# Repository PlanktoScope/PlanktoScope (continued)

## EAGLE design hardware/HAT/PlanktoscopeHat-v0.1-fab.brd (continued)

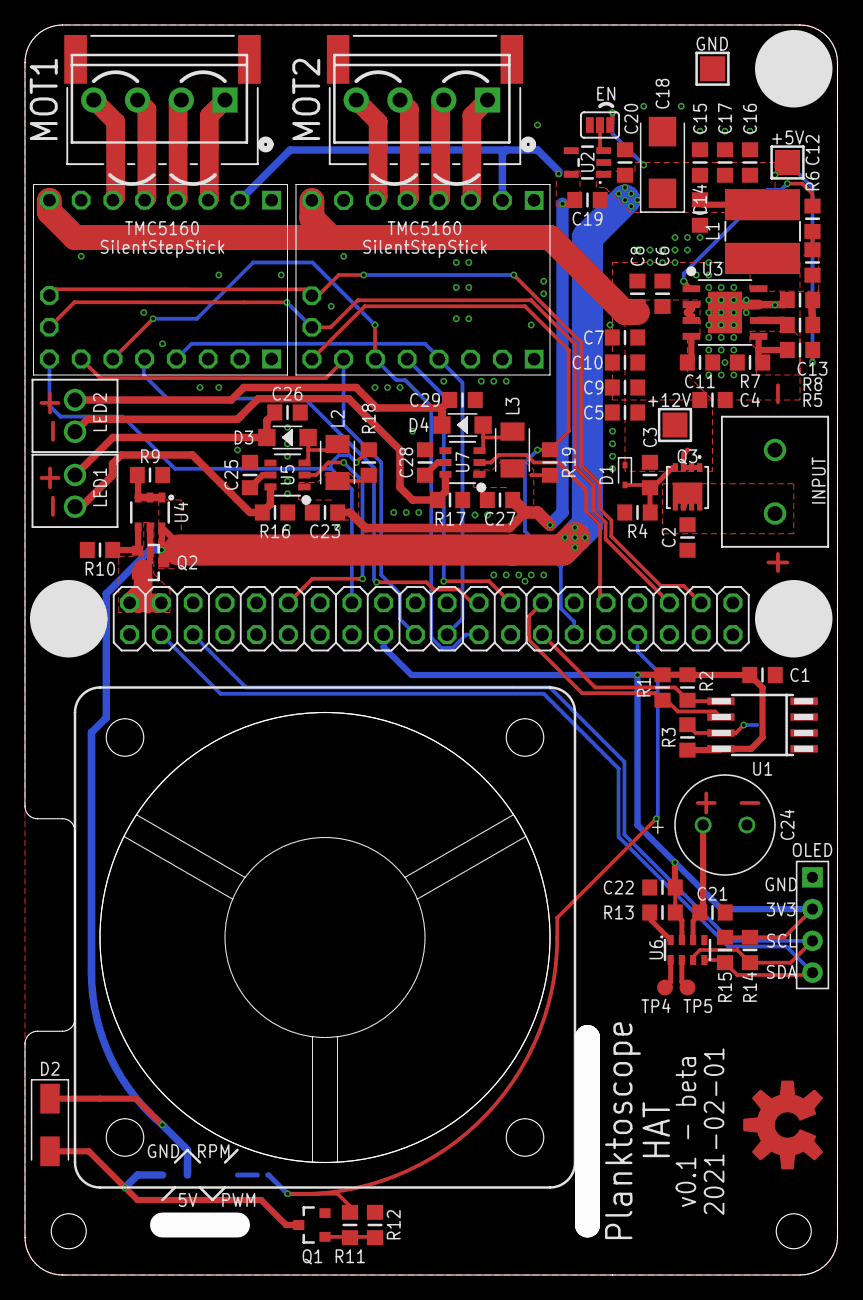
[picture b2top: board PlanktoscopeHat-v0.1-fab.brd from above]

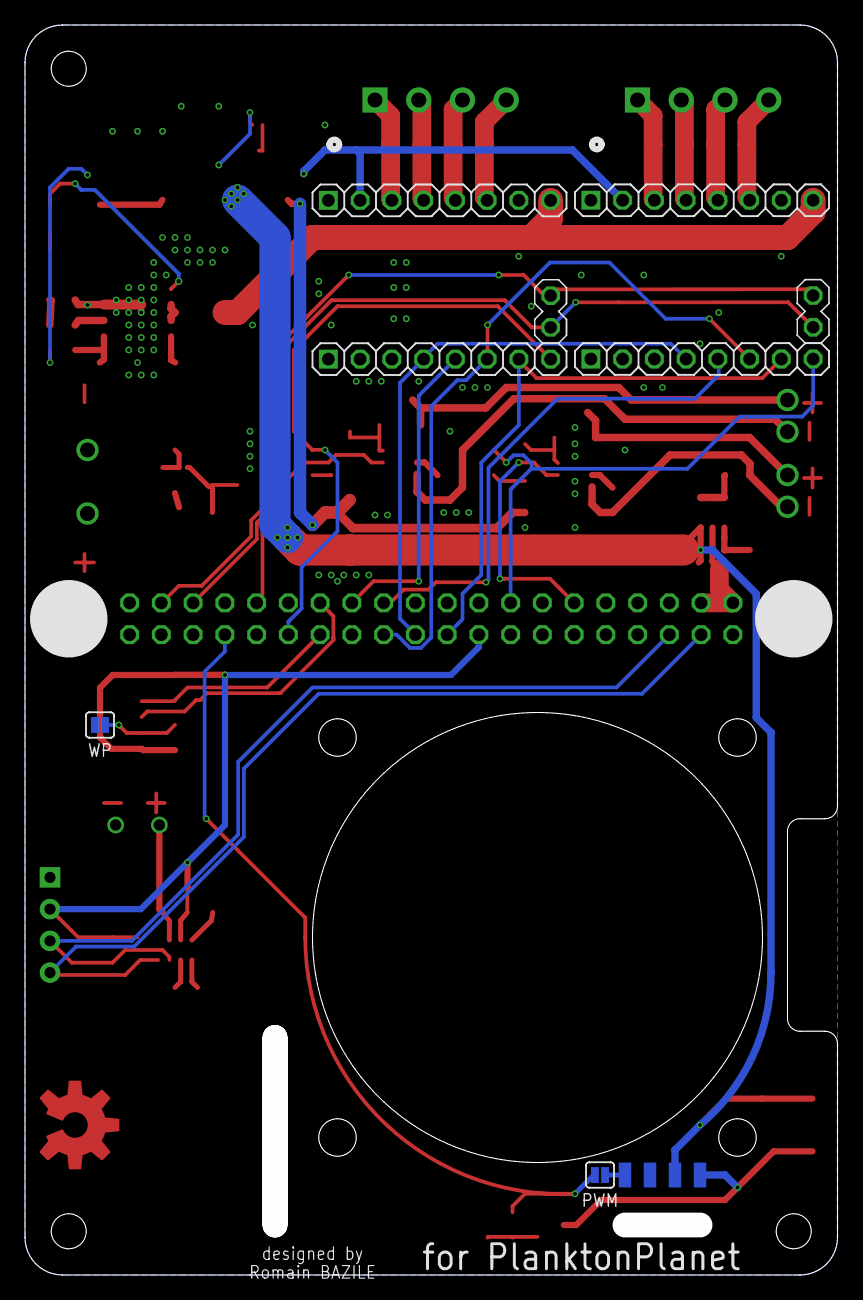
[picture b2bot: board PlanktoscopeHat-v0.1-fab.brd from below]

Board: 2 copper layers, 65.0 x 100.0 mm, 90 parts (8 on the bottom side), 58 nets.

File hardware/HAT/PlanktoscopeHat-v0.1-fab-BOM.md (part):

Qty|Value             |Device                      |Package             |Parts                          |Description                                       |MPN                  |Order Link |Alternative MPN | Alternative Order Link
:-:|----------------|----------------------------|--------------------|-------------------------------|--------------------------------------------------|---------------------|-----------|----------------|-----------------------
1  |1.2nF             |Capacitor Ceramic           |0805                |C13                            |Ceramic Capacitors                                |C0805C122K5RACTU     |https://www.mouser.fr/ProductDetail/KEMET/C0805C122K5RACTU/?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|                |
7  |100nF 100V        |Capacitor Ceramic           |0805                |C1, C2, C3, C11, C12 , C21, C22|Ceramic Capacitors                                |CL21B104KCFSFNE      |https://www.mouser.fr/ProductDetail/Samsung-Electro-Mechanic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 | |
2  |220nF             |Capacitor Ceramic           |0805                |C25, C28                       |Ceramic Capacitors                                |CL21B224KBFNNNG      |https://www.mouser.fr/ProductDetail/Samsung-Electro-Mechanic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 | | 
5  |10uF              |Capacitor Ceramic           |0805                |C14, C15, C16, C17, C19        |Ceramic Capacitors                                |CL21A106KOQNNNG      |https://www.mouser.fr/ProductDetail/Samsung-Electro-Mechanic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 | |
7  |10uF 35V          |Capacitor Ceramic           |0805                |C4, C5, C6, C7, C8, C9, C10    |Ceramic Capacitors                                |GRM21BR61H106KE43L   |https://www.mouser.fr/ProductDetail/Murata-Electronics/GRM21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 | |
1  |100µF 10VDC       |Capacitor Polarised Tantalum|2412 (6032 metric)  |C18                            |Capacitor Polarised                               |TPSC107K010T0200     |https://www.mouser.fr/ProductDetail/AVX/TPSC107K010T0200/?qs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 | |
3  |1µF               |Capacitor Ceramic           |0805                |C26, C29, C20                  |Ceramic Capacitors                                |CL21B105KAFNFNE      |https://www.mouser.fr/ProductDetail/Samsung-Electro-Mechanic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 | | 
2  |4.7µF             |Capacitor Ceramic           |0805                |C23, C27                       |Ceramic Capacitors                                |CL21A475KAQNNNG      |https://www.mouser.fr/ProductDetail/Samsung-Electro-Mechanic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 | | 
1  |1F-10F 3V         |Supercap                    |8X3.5X0.9           |C24                            |WCAP-PTHT Aluminum Polymer Capacitors             |DSF106Q3R0           |https://www.mouser.fr/ProductDetail/Cornell-Dubilier-CDE/DSF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 |SCCR16E205PRB |https://www.mouser.fr/ProductDetail/AVX/SCCR16E205PRB/?qs=qS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
2  |2R / 10R          |Resistor                    |0805                |R16, R17                       |Resistors                                         |CRCW08052R00FKEA     |https://www.mouser.fr/ProductDetail/Vishay-Dale/CRCW08052R00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 | | 
1  |10R               |Resistor                    |0805                |R6                             |Resistors                                         |CRCW080510R0FKEAC    |https://www.mouser.fr/ProductDetail/Vishay-Dale/CRCW080510R0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 | |
1  |499R              |Resistor                    |0805                |R11                            |Resistors                                         |CR0805-FX-4990ELF    |https://www.mouser.fr/ProductDetail/Bourns/CR0805-FX-4990ELF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 | | 
1  |1k                |Resistor                    |0805                |R3                             |Resistors                                         |CRCW08051K00FKEAC    |https://www.mouser.fr/ProductDetail/Vishay-Dale/CRCW08051K00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 | | 
1  |2.2k 1%           |Resistor                    |0805                |R7                             |Resistors                                         |CRCW08052K20FKEA     |https://www.mouser.fr/ProductDetail/Vishay-Dale/CRCW08052K20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 | | 
2  |3.9k              |Resistor                    |0805                |R1, R2                         |Resistors                                         |CRCW08053K90FKEA     |https://www.mouser.fr/ProductDetail/Vishay-Dale/CRCW08053K90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 | | 
1  |4.99k             |Resistor                    |0805                |R12                            |Resistors                                         |CRCW08054K99FKEAC    |https://www.mouser.fr/ProductDetail/Vishay-Dale/CRCW08054K99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 | | 
6  |10k 1%            |Resistor                    |0805                |R9, R13, R14, R15, R18, R19    |Resistors                                         |CRCW080510K0FKEAC    |https://www.mouser.fr/ProductDetail/Vishay-Dale/CRCW080510K0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 | |
2  |12k 1%            |Resistor                    |0805                |R4, R5                         |Resistors                                         |CRCW080512K0FKEA     |https://www.mouser.fr/ProductDetail/Vishay-Dale/CRCW080512K0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 | |
1  |20k 1%            |Resistor                    |0805                |R8                             |Resistors                                         |CRCW080520K0FKEAC    |https://www.mouser.fr/ProductDetail/Vishay-Dale/CRCW080520K0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 | | 
1  |47k 1%            |Resistor                    |0805                |R10                            |Resistors                                         |CRCW080547K0FKEAC    |https://www.mouser.fr/ProductDetail/Vishay-Dale/CRCW080547K0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 | | 
1  |40MM_FAN          |FAN PWM Control             |40MM_FAN            |FAN                            |                                                  |NF-A4x10 5V PWM      |https://www.amazon.fr/NF-A4x10-5V-PWM-Ventilateur-silencieux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 | | 
2  |2828XX-2282834-2  |2828XX-2282834-2            |TERMBLK_254-2N      |LED1, LED2                     |2 Position Wire to Board Terminal Block           |282834-2             |https://fr.farnell.com/buchanan-te-connectivity/282834-2/ter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 |1814841 + 1814980 |https://www.mouser.fr/ProductDetail/Phoenix-Contact/1814841/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 + 
1  |2828XX-2282837-2  |2828XX-2282837-2            |TERMBLK_508-2N      |INPUT                          |2 Position Wire to Board Terminal Block           |TC0203620000G        |https://www.mouser.fr/ProductDetail/Amphenol-Anytek/TC020362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 |1792863|https://www.mouser.fr/ProductDetail/Phoenix-Contact/1792863/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 
1  |2x20pins 2.54mm   |Stacking header             |2x20                |K1                             |Stacking pin header                               |M20-6102045          |https://fr.farnell.com/harwin/m20-6102045/fiche-femelle-pc-1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 | | 
2  |2pins 2.54mm      |Female Header Vertical      |1x2                 |P6, P9                         |Pin Header                                        |801-87-040-10-001101 |https://www.mouser.fr/ProductDetail/Preci-dip/801-87-040-10-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 | | 
4  |8pins 2.54mm      |Female Header Vertical      |1x8                 |P4, P5, P7, P8                 |Pin Header                                        |combined with above  | | | 
1  |4pins 2.54mm      |Female Header Vertical      |1x4                 |OLED                           |Pin Header                                        |combined with above  | | | 
2  |S4B-XH-SM4-TB     |4pin SMD connector          |S4B-XH-SM4-TB_JST   |MOT1, MOT2                     |                                                  |S4B-XH-SM4-TB(LF)(SN)|https://fr.farnell.com/jst-japan-solderless-terminals/s4b-xh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 | | 
2  |40V 500MA         |Diode Schottky              |SOD-123             |D3, D4                         |B0540W                                            |B0540W-7-F           |https://www.mouser.fr/ProductDetail/Diodes-Incorporated/B054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 | | 
2  |10µH              |Inductor molded             |1210 (3225 metric)  |L2, L3                         |Inductor                                          |CBC3225T100KR        |https://www.mouser.fr/ProductDetail/Taiyo-Yuden/CBC3225T100K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 | |
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
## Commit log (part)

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2025-11-12 controller: Allow changing bubbler and light intensity
2025-11-12 read status
2025-11-13 plenty of stuff
2025-11-13 controller: Make bubbler/led intensity variable (#815)
2025-11-13 controller: Record led operating time
2025-11-17 setup ccm
2025-11-17 controller: Fix light for 2.6
2025-11-17 Do not enable nodered
2025-11-17 infra: Update GitHub actions runner (#816)
2025-11-18 ecotaxa my files API renamed
2025-11-18 scripts
2025-11-19 backend: Add reset API
2025-11-19 os: Simplify hostname
2025-11-19 Remove adafruithat support
2025-11-19 os: Simplify hostname (#818)
2025-11-19 controller: Use a normalized value for light
2025-11-20 Scan wifi
2025-11-20 test
2025-11-24 remove dead code
2025-11-24 Remove planktoscopehat Node-RED project
2025-11-25 min_size
2025-11-25 segmenter: Use ESD and make it configurable (#814)
2025-11-25 segmenter: process_min_object_size -> process_min_ESD
2025-11-25 Remove remaining 2.1 stuff
2025-11-25 controller: Default light/bubbler "on" value to 1
2025-11-25 lib: Make reboot and poweroff always work
2025-11-26 eeprom
2025-11-26 Record LED operating time (#636)
    For the [dashboard 2 "Lightness" calibration
    page](https://www.figma.com/design/KXH3qkalr7eeFbyGsutZKt/PlanktoScope-Dashboard-v2?node-id=1000-616&m=dev)
2025-11-26 setup: Do not ask user for hardware version
2025-11-26 backend: prevent startup crash on v2.6
2025-11-26 os: Use RPI OS 2025-11-24 as base
2025-11-27 os: Use RPI OS 2025-11-24 as base and bug fixes (#825)
2025-11-27 os: Build image scripts
2025-12-02 Make changes as requested
2025-12-02 wait a bit for light to be on
2025-12-02 segmenter: Remove mjpeg stream
2025-12-02 segmenter: Make remove previous mask optional and disabled by default
2025-12-02 segmenter: Make remove previous mask optional and disabled by default (#830)
2025-12-03 lib: Walk directories and count images acquired acurately
2025-12-08 Update CHANGELOG and Test Suite
2025-12-09 first test
2025-12-09 rework for tests
2025-12-11 Update CHANGELOG (#831)
2025-12-15 lib: Limit timezone options
2025-12-15 backend: Set hardware version from factory page
2026-01-05 controller: Use SPI1 for display
2026-01-07 progress
2026-01-08 os: Document and add image building scripts (#827)
2026-01-08 node-red: Remove unused dependencies
2026-01-08 node-red: Remove unused deps (#834)
2026-01-08 os: Remove unused bluez in postinstall
2026-01-08 controller: Use SPI1 for display (#833)
2026-01-08 Set hardware version during factory
2026-01-12 controller: Introduce async pump service (#804)
2026-01-12 controller: Introduce async focus service
2026-01-12 controller: Introduce async focus service (#837)
    Similar to #804
2026-01-12 controller: Extract imager
2026-01-12 controller: Update README
2026-01-12 controller: Move camera to its own service
2026-01-14 remove stop_event it is never set
2026-01-14 Use Task Group for aiomqtt
    https://textual.textualize.io/blog/2023/02/11/the-heisenbug-lurking-in-your-async-code/
2026-01-14 controller: Make imager return acquisition path
2026-01-15 Improve preview reliability
2026-01-15 Fix issue with no preview at boot (#841)
2026-01-19 os: Prototype with exfat for data
2026-01-20 segmenter: Add simple test file
2026-01-21 os: Disable swap
2026-01-21 dev: Add git hook to run just test on push on main
2026-01-22 os: Use a shallow clone to reduce size on disk
2026-01-22 os: Use cloud-init and adjust scripts/docs
2026-01-26 build(deps): bump library/python
    Bumps the deps group with 1 update in the /segmenter directory: library/python.
    Updates `library/python` from 3.13-slim-trixie to 3.14-slim-trixie
    build(deps): bump the deps group across 4 directories with 18 updates
    Bumps the deps group with 6 updates in the /backend directory:
    | Package | From | To |
    | --- | --- | --- |
2026-01-28 controller: Implement display machine name
2026-01-29 add brand, progress, online
2026-01-30 fix Segmentation: Add skewness and kurtosis calculation #103
2026-01-30 fix Solve the FIXME: just use python's csv library, to shave off pandas's 60 MB of unnecessary disk space usage #846
2026-02-02 Use UUIDs instead of machine name (#849)
    # What
    Use generated UUIDs for `acq_uuid`, `sample_uuid` and `process_uuid`
    instead of the machine name.
    They will look something like `b5515a78-6196-4841-a5a8-315b9b98f2af`
    instead of `sponge-bob-12345`.
    https://en.wikipedia.org/wiki/Universally_unique_identifier
2026-02-02 segmenter: Allow running locally
2026-02-02 segmenter: Allow running locally (#850)
    Depends on https://github.com/PlanktoScope/PlanktoScope/pull/849
    # What
    * Allow running the segmenter locally, without a container.
    * Remove containerized segmenter
    # Why
    * Simplify development / testing and using the segmenter on computers
2026-02-02 fix: H.264 video stream corruption on RPi5
    Fix severe video corruption/pixelization in the live stream on Raspberry Pi 5.
    - Change RPi5 preview resolution from 2028x1520 to 1920x1440 (16-pixel aligned)
    - Use baseline H.264 profile to disable B-frames for WebRTC compatibility
    - Add writeQueueSize: 1024 to mediamtx to prevent packet drops
    References:
    - https://github.com/bluenviron/mediamtx/issues/3022
2026-02-02 fix: prevent calibration settings loss on restart
    Reduce Node-RED context storage flush interval from 30s to 5s.
    This prevents calibration data loss when Node-RED restarts before
    the default 30-second flush completes.
2026-02-03 draw FairScope logo
2026-02-03 poweroff
2026-02-03 controller: Implement display (#851)
2026-02-03 os: Remove /run/machine-name
2026-02-03 rework comments to avoid future mislead
2026-02-03 Remove decommissioned Mozilla stun server
    https://bugzilla.mozilla.org/show_bug.cgi?id=1324520
2026-02-03 Revert "preview: Optimize H.264 video stream (#852)"
    This reverts commit 914f5e89f0b436e0e57f9750a58a6fde336335c4.
2026-02-04 preview: Tweak sysctl to remove packet loss between MediaMTX and picamera2
    This should solve corrupted frames
    Follow up to https://github.com/PlanktoScope/PlanktoScope/pull/852
2026-02-04 preview: Remove decommissioned stun server
    https://bugzilla.mozilla.org/show_bug.cgi?id=1324520
2026-02-04 controller: Document bubbler API
2026-02-04 controller: Remove IMX219 support
2026-02-04 lib: Fix setHardwareVersion
2026-02-04 segmenter: Fix uuid serialization
2026-02-05 controller: Do not retain MQTT messages
2026-02-09 controller: Make camera fsync when capturing files (#858)
    Based on suggestion from @babo989 at
    https://github.com/PlanktoScope/PlanktoScope/pull/854
    ---
2026-02-09 os: Do not perform shallow clone for setup
    It breaks `getSoftwareVersion` with ExecaError: Command failed with exit code 128: git describe --tags --match 'software/v*' --dirty --broken
2026-02-09 fix: adjust pump logic for low volume
2026-02-09 controller: adjust pump logic for low volume (#859)
    ---------
2026-02-10 os: Add mediamtx webrtcAdditionalHosts
    This fixes the WeRTC connectivity issue with
    * Windows
    * Chrome
    * No Tailscale
    * 192.168.4.1
    It also appears to solve it for local DNS (http://planktoscope-sponge-bob)
2026-02-10 segmenter: Fix PLANKTOSCOPE_DATA_PATH
2026-02-10 lib: Improve getGalleryPath
2026-02-10 Fix pump calibration not saving to hardware.json
    - Connect calibration save flow to file write nodes
    - Read existing hardware.json before updating to preserve other settings
    - Load current pump_steps_per_ml into UI on page load
    - Add live MQTT config updates so calibration applies without restart
    - Add debug logging to pump controller
    Fixes: calibration values were lost because the Node-RED flow had a disconnected wire, and the UI was using a hardcoded default (507) instead of the actual value from hardware.json
2026-02-10 Update default pump calibration to 3408 steps/ml. Calibrated value determined through physical measurement.
2026-02-10 controller: Configure pump (#863)
    Calibration comes from
    https://github.com/fairscope/PlanktoScope3/issues/413
2026-02-11 Add ramp mode for bubbler to provide consistent gentle agitation
    The bubbler air pump motor has a minimum operating voltage threshold
    (~0.265). Below this, the motor stalls. Above it, continuous operation
    was too fast for gentle sample agitation.
    This implements a ramp pattern that:
    - Cycles through configurable voltage levels (default: 0.26-0.275)
    - Ramps up, then down, then pauses with motor off
2026-02-11 os: Use Wi-Fi 5GHz for AP
2026-02-11 Fix formatting: add space after comment marker
2026-02-11 os: Use Wi-Fi 5GHz for AP (#865)
    Unfortunately the Raspberry does not support dual channel mode so we
    have to choose between 2.4GHz and 5GHz.
    5GHz is more stable and higher bandwidth. Its downside is a reduced
    range but for our use case it shouldn't be a problem.
    Approximately all laptop since ~ 2010 support WiFi 5 GHz. I would like
    to get this in the beta so we can see if anyone encounters problems.
2026-02-11 os: Fix wifi name when using just
2026-02-11 segmenter: Fix PLANKTOSCOPE_DATA_PATH (#861)
2026-02-11 os: Remove pkscope hostname and tld (#866)
    Removes `x.pkscope` and `pkscope.x` hostnames.
2026-02-11 fix: correct pump flow rate timing with TMC5160 velocity factor
    The TMC5160 stepper driver uses internal velocity units where:
    \_velocity = VMAX \times (fCLK / 2^{24})$
    With the internal oscillator (~12 MHz), setting VMAX directly to the
    desired microsteps/second results in the motor running ~28% slower
    than expected (e.g., 1ml/min taking 80 seconds instead of 60).
    This fix adds a velocity conversion factor (^{24}/fCLK \approx 1.398$) to
2026-02-12 Move pump timing fix from pump to motor controller
2026-02-12 controller: correct pump flow rate timing with TMC5160 velocity factor (#867)
    **Problem:** When users set 1ml/min flow rate, the pump took ~80 seconds
    instead of 60 seconds.
    **Root Cause:** The TMC5160 stepper driver doesn't interpret VMAX
    register values as direct microsteps/second. It uses internal time units
    based on its clock frequency:
    **actual_velocity** = VMAX × (fCLK / 2^24)
2026-02-12 lib: Add date to listSegmentations and listAcquisitions
2026-02-12 lib: Make listSegmentations and listAcquisitions return dates (#869)
    There are several issues with this
    **segmentation**
    segmentations currently don't have a date so I'm using the creation date
    of the folder.
    this works ok if the segmentation was done on the PlanktoScope but the
    creation date of the folder can be lost if it was transferred from an
2026-02-15 Redesign e-paper display layout with the new branding
2026-02-16 Add live segmentation with real-time preview and blur metrics
2026-02-16 Update dashboard UI: styling, calibration, navigation, QT Py Remote
2026-02-16 Update controller defaults for focus, pump, light, and imager
2026-02-16 Address review: remove the unrelated changes, let blur errors throw
2026-02-16 Add autofocus sweep feature with MQTT control and dashboard button
2026-02-16 The bubbler is now on/off
2026-02-16 controller: Use ramp mode for Bubbler (#864)
    ## Summary
    - Implements ramp-based bubbler control for gentle, consistent sample
    agitation
    - Motor cycles through voltage levels (0.26 → 0.275 → off → pause →
    repeat)
    - Solves motor stall issues at low voltages and provides smoother
2026-02-16 segmenter: add blur metric for segmented objects (#860)
    # Blur Metric Validation Report
    ## Overview
    This document validates the Laplacian variance blur metric
    implementation added to the PlanktoScope segmenter. The metric
    calculates focus quality for each segmented object and writes it to the
    EcoTaxa TSV export as `object_blur_laplacian`. It was tested on a small
2026-02-16 Small doc tweaks
2026-02-17 Update imager controller and dashboard flows
2026-02-17 remove unused file
2026-02-17 controller: Redesign e-paper display layout (#870)
2026-02-17 Fixed Flatfield correction to run before saving images
2026-02-18 Added minimum diameter feature when live seg is enabled.
2026-02-18 Use npm ci instead of npm install
    It locks `package-lock.jon` wich prevents conflicts when updating
2026-02-19 controller: Do not clear display on power off
2026-02-19 Sonny is pushing, no idea what it does :)
